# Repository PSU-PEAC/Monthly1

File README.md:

Monthly1
========

5A Constant Voltage/Constant Current Regulator

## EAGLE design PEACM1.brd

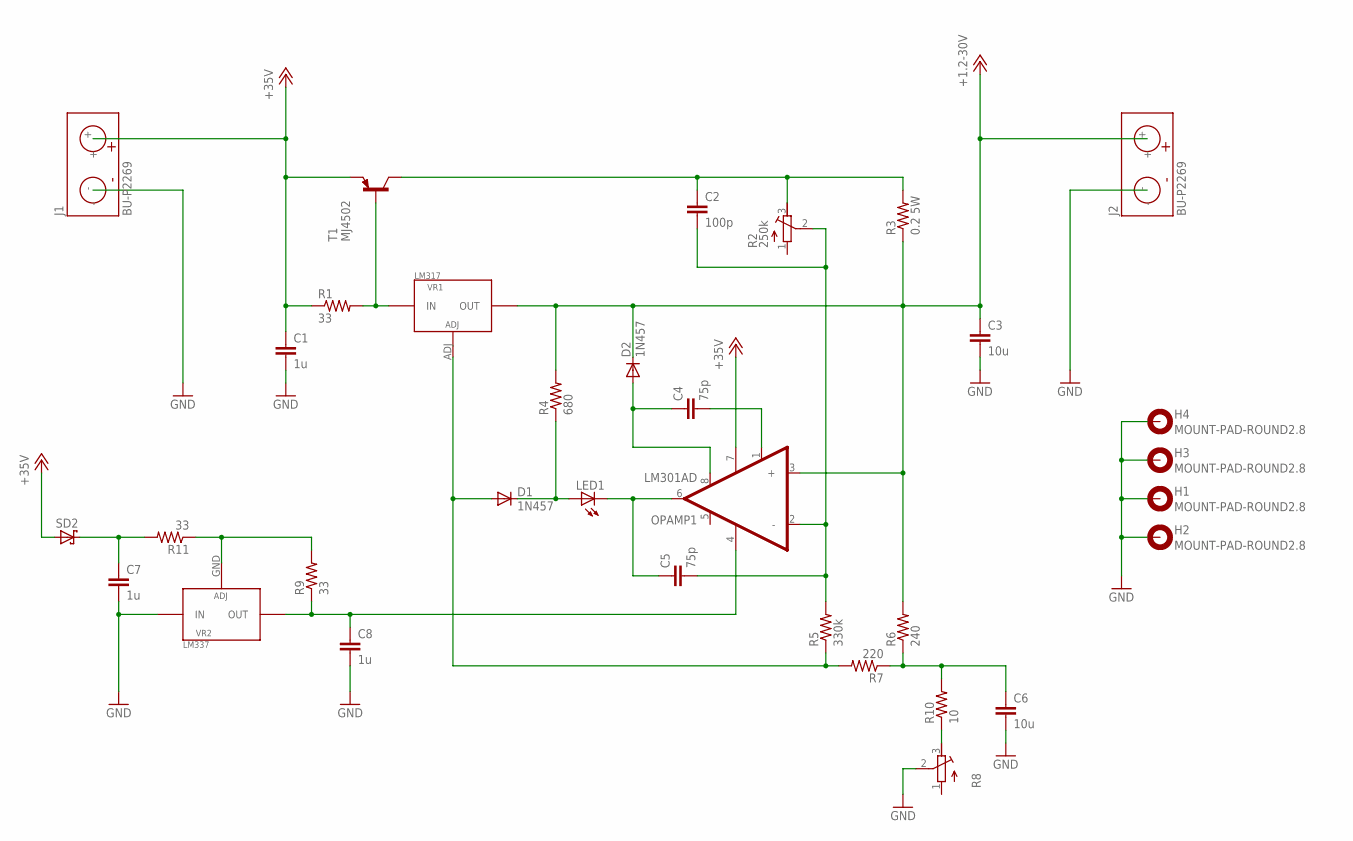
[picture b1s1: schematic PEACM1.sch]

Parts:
C1, C7, C8: 1u; C0805
C2: 100p; C0805
C3, C6: 10u; C0805
C4, C5: 75p; C0805
D1, D2: 1N457; DO35-10
H1, H2, H3, H4: MOUNT-PAD-ROUND2.8; 2,8-PAD
J1, J2: BU-P2269
LED1: LEDCHIPLED_1206; CHIPLED_1206
OPAMP1: LM301AD; SOIC8
R1, R9, R11: 33; M1206
R2: 250k; RTRIM4G/J
R3: 0.2 5W; R4527
R4: 680; M1206
R5: 330k; M1206
R6: 240; R1206
R7: 220; R1206
R8: R-TRIMM4G/J; RTRIM4G/J
R10: 10; R1206
SD2: STPS0540Z; SOD-123
T1: MJ4502; TO3
VR1: LM317; D2PAK-3
VR2: LM337; DPAK(TO-252)

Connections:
+1.2-30V: C3.1, D2.C, J2.+, OPAMP1.3 (+), R3.1, R4.2, R6.2, VR1.VOUT (OUT)
+35V: C1.1, J1.+, OPAMP1.7 (VCC+), R1.1, SD2.A, T1.E
EMITTER_RES: C2.1, R2.3 (E), R3.2, T1.C
GND: C1.2, C3.2, C6.2, C7.2, C8.2, H1.B2,8, H2.B2,8, H3.B2,8, H4.B2,8, J1.-, J2.-, R8.2 (S), VR2.INPUT (IN)
unnamed: C4.2, OPAMP1.1 (BAL#1)
unnamed: C7.1, R11.2, SD2.C
unnamed: R1.2, T1.B, VR1.VIN (IN)
unnamed: C2.2, C5.2, OPAMP1.2 (-), R2.2 (S), R5.2
unnamed: D1.A, R5.1, R7.2, VR1.ADJ
unnamed: R8.3 (E), R10.1
unnamed: C6.1, R6.1, R7.1, R10.2
unnamed: D1.C, LED1.A, R4.1
unnamed: C4.1, D2.A, OPAMP1.8 (BAL)
unnamed: C5.1, LED1.C, OPAMP1.6 (OUT_A)
SCH_RES_VCC-: R9.2, R11.1, VR2.GND (ADJ)
VCC-: C8.1, OPAMP1.4 (VCC-), R9.1, VR2.OUTPUT (OUT)

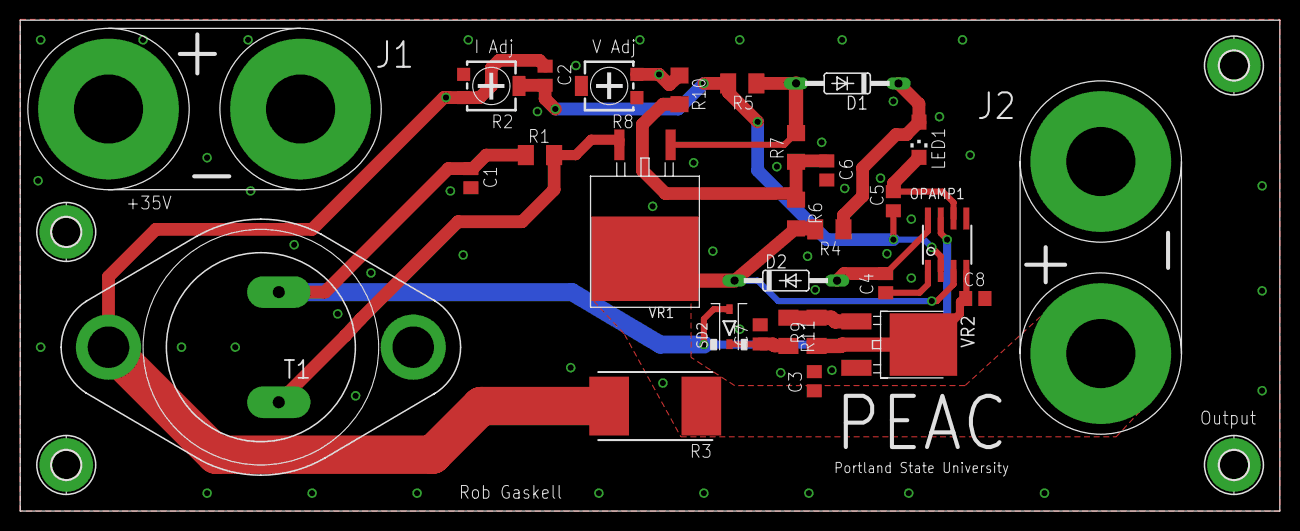
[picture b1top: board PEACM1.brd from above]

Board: 2 copper layers, 124.9 x 48.7 mm, 33 parts (0 on the bottom side), 16 nets.

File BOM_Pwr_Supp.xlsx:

Schematic Part# | Nomenclature/Value | Package | Digikey PN | Price/unit | Mouser PN | Price/unit
R1 | 33 Ohm, 1/8W | 0805 SMD | 311-33.0CRCT-ND | 0.1
R2 | 250k Ohm Pot, 1/2W | See web | 3361P-1-254GLFCT-ND | 1.27
R3 | 0.2 Ohm, 5W | 4527 SMD | WSRC-.2CT-ND | 2.63
R4 | 680 Ohm, 1/8W | 0805 SMD | 311-680ARCT-ND | 0.1
R5 | 330k Ohm, 1/8W | 0805 SMD | 311-330KARCT-ND | 0.1
R6 | 240 Ohm, 1/8 W | 0805 SMD | RMCF0805JT240RCT-ND | 0.03
R7 | 220 Ohm, 1/8W | 0805 SMD | RMCF0805JT220RCT-ND | 0.03
R8 | ?? Ohm Pot |  | 150k or 1.2k
R10 | 20 Ohm, | 0805 SMD | 1276-5487-1-ND | 0.1
C1 | 1 uF Electrolytic | Thru-Hole | P15831CT-ND | 0.35
C2 | 100 pF, 50V, 10% | 0805 SMD | 399-1121-1-ND | 0.1
C3 | 10 uF Electrolytic | Thru-Hole | P5567-ND | 0.23
C4 | 75 pF, 50V, 5% | 0805 SMD | 1276-2690-1-ND | 0.25
C5 | 75 pF, 50V, 5% | 0805 SMD | 1276-2690-1-ND | 0.25
C6 | 10 uF Electrolytic | Thru-Hole | P5567-ND | 0.23
D1 | 1N457 | Thru-Hole | 1N457CT-ND | 0.17
D2 | 1N457 | Thru-Hole | 1N457CT-ND | 0.17
D3 | Red LED | 0805 SMD | 160-1178-1-ND | 0.36
Q1 | MJ4502, PNP BJT | TO-3 | MJ4502GOS-ND | 4.29
U1 | LM317k, Voltage Reg | DDPAK | 296-21390-1-ND | 0.99
U2 | LM301A | 8-SOIC | 497-7819-1-ND | 0.89
J1 | Banana Jack |  | 314-1204-ND | 3.32
J2 | Banana Jack |  | 314-1204-ND | 3.32
 | Heat Sink for BJT |  | Individual buys
 |  |  | Total: | 19.28

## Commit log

2014-04-12 Initial check-in.
2014-04-12 Schematic components from example complete. Needs connectors, V+ for OpAmp.
2014-04-13 Schematic and layout ready for review.
2014-04-18 Completed board layout.
2014-04-19 BOM for project 1, updated 4/19/14
2014-04-20 Added -6V regulator, banana jacks.
